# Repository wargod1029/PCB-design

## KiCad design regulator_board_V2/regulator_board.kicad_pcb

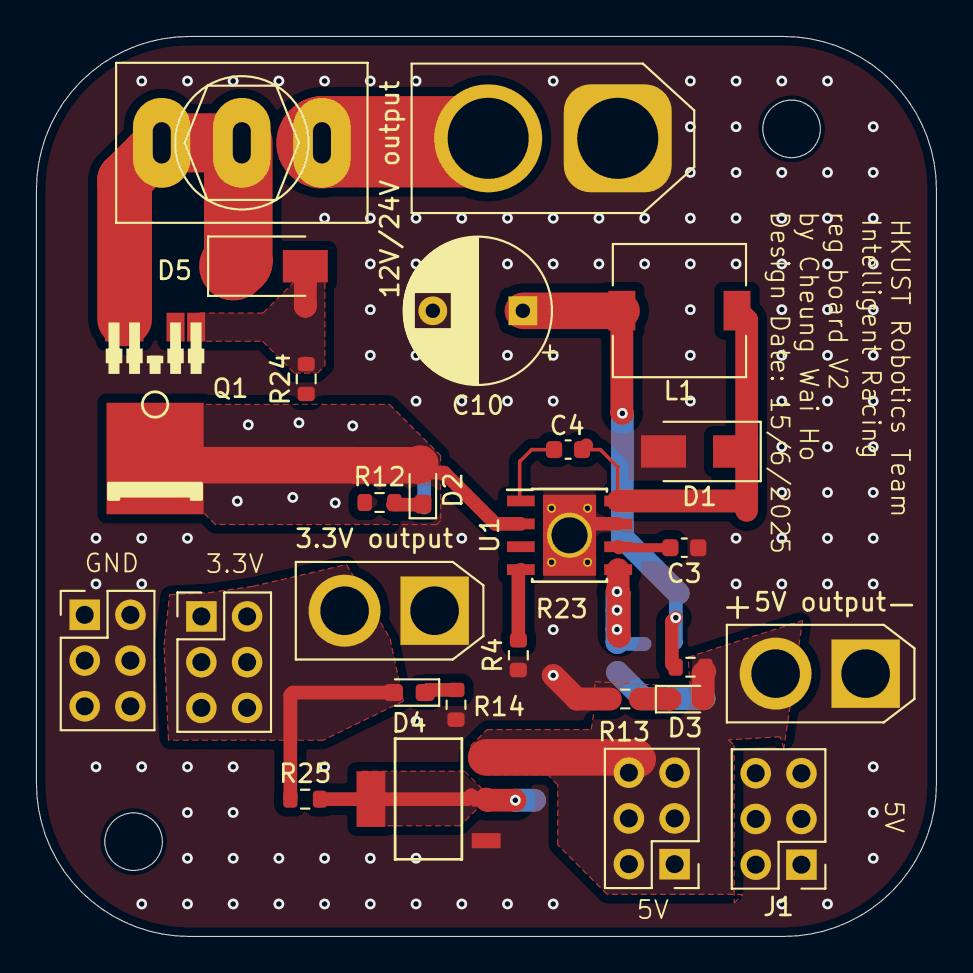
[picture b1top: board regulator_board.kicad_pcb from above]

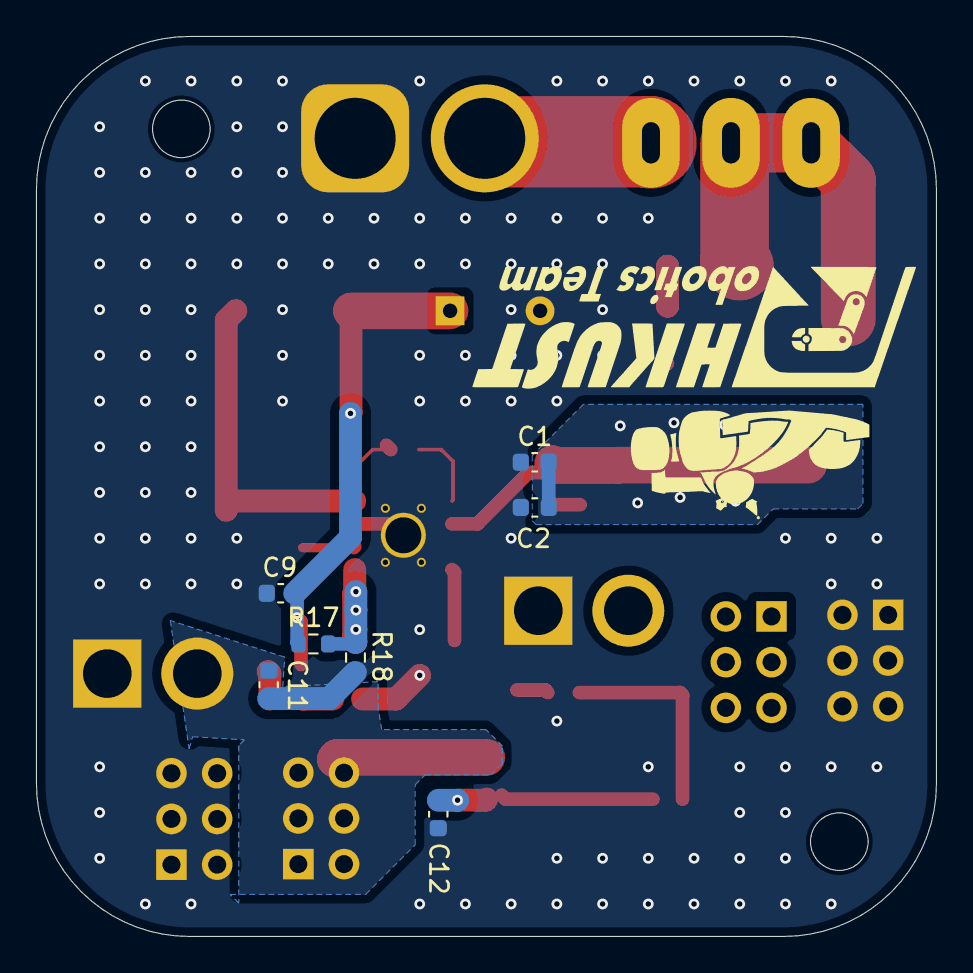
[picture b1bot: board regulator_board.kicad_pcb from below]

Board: 2 copper layers, 50.0 x 50.0 mm, 36 parts (7 on the bottom side), 17 nets.

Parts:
C1, C2: 2.2uF; C_0603_1608Metric
C3: 39pF; C_0603_1608Metric
C4: 100nF; C_0603_1608Metric
C9, C11, C12: 10uF; C_0603_1608Metric
C10: 10V 1000uF; CP_Radial_D8.0mm_P12.00mm
D1, D5: SS54; D_SMA
D2: 24V; LED_0603_1608Metric_Pad1.05x0.95mm_HandSolder
D3: 5V; LED_0603_1608Metric_Pad1.05x0.95mm_HandSolder
D4: 3.3V; LED_0603_1608Metric_Pad1.05x0.95mm_HandSolder
H2, H3: MountingHole; MountingHole_3.2mm_M3
J1, J3, J5, J6: Conn_02x03_Odd_Even_MountingPin; PinHeader_2x03_P2.54mm_Vertical
J2: 5V output; AMASS_XT30U-F_1x02_P5.0mm_Vertical
J4: 3.3V output; AMASS_XT30U-F_1x02_P5.0mm_Vertical
J7: Conn_01x02; AMASS_XT60-M_1x02_P7.20mm_Vertical
L1: 22uH; L_7.3x7.3_H3.5
Q1: SPD50P03LG; TO252-51
R4: 162k; R_0603_1608Metric
R12: 2.5k; R_0603_1608Metric
R13: 2k; R_0603_1608Metric
R14: 1.5k; R_0603_1608Metric
R17: 53.6k; R_0603_1608Metric
R18: 10.2k; R_0603_1608Metric
R23, R25: 0R; R_0603_1608Metric
R24: 10k; R_0603_1608Metric
SW1: 24V input; SW_Toggle_Blue_wSlots
U1: TPS54360DDA; TI_SO-PowerPAD-8_ThermalVias
U6: LM1117-3.3; SOT230

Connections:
+3.3V: D4.2 (A), J4.2, J5.1, J5.2, J5.3, J5.4, J5.5, J5.6, R25.1
+5V: C11.1, D3.2 (A), J2.2, J3.1, J3.2, J3.3, J3.4, J3.5, J3.6, R23.1, U6.3 (VIN)
+24V: C1.2, C2.2, D2.2 (A), Q1.5, U1.2 (VIN)
/FB: R17.1, R18.2, U1.5 (FB)
/Vin: D5.1 (K), Q1.3, Q1.4, SW1.2 (B), SW1.3 (C)
GND: C1.1, C2.1, C3.1, C9.2, C10.2, C11.2, C12.2, D1.2 (A), J1.1, J1.2, J1.3, J1.4, J1.5, J1.6, J2.1, J4.1, J6.1, J6.2, J6.3, J6.4, J6.5, J6.6, J7.1, R4.1, R12.1, R13.1, R14.1, R18.1, R24.1, U1.7 (GND), U1.9 (GNDPAD), U6.1 (ADJ/GND)
unnamed: C9.1, C10.1, L1.2, R17.2, R23.2
unnamed: C4.1, D1.1 (K), L1.1, U1.8 (SW)
unnamed: D2.1 (K), R12.2
unnamed: D3.1 (K), R13.2
unnamed: D4.1 (K), R14.2
unnamed: D5.2 (A), Q1.1, R24.2
unnamed: J7.2, SW1.1 (A)
unnamed: C4.2, U1.1 (BOOT)
unnamed: C3.2, U1.6 (COMP)
unnamed: R4.2, U1.4 (RT/CLK)
unnamed: C12.1, R25.2, U6.2 (VOUT), U6.4 (VOUT_2)

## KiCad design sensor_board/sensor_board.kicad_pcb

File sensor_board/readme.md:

# sensor_board

Brief
- 7 Infered sensors design for use in Forklift robot in Taiwan AERC competition

Key features
- Direct output analog signal from XH pin header

Repository structure
- `sensor_board.kicad_pcb` — PCB layout
- `sensor_board.kicad_sch` — Schematic
- `sensor_board.kicad_pro` — KiCad project file

Electrical overview (fill with measured values)
- Supply voltage: 3.3V to 5V

Connectors & pins
- POWER: VCC, GND
- SENSOR: direct analog voltage output (IR1 - IR7)

Fabrication notes
- PCB thickness: 1.6 mm
- Layer count: 2
- Copper thickness: 1 oz external

BOM
- Use KiCad's BOM export (`bom` plugin)

KiCad / development notes
- KiCad version used: 8.0

Designer
- Andy, Cheung

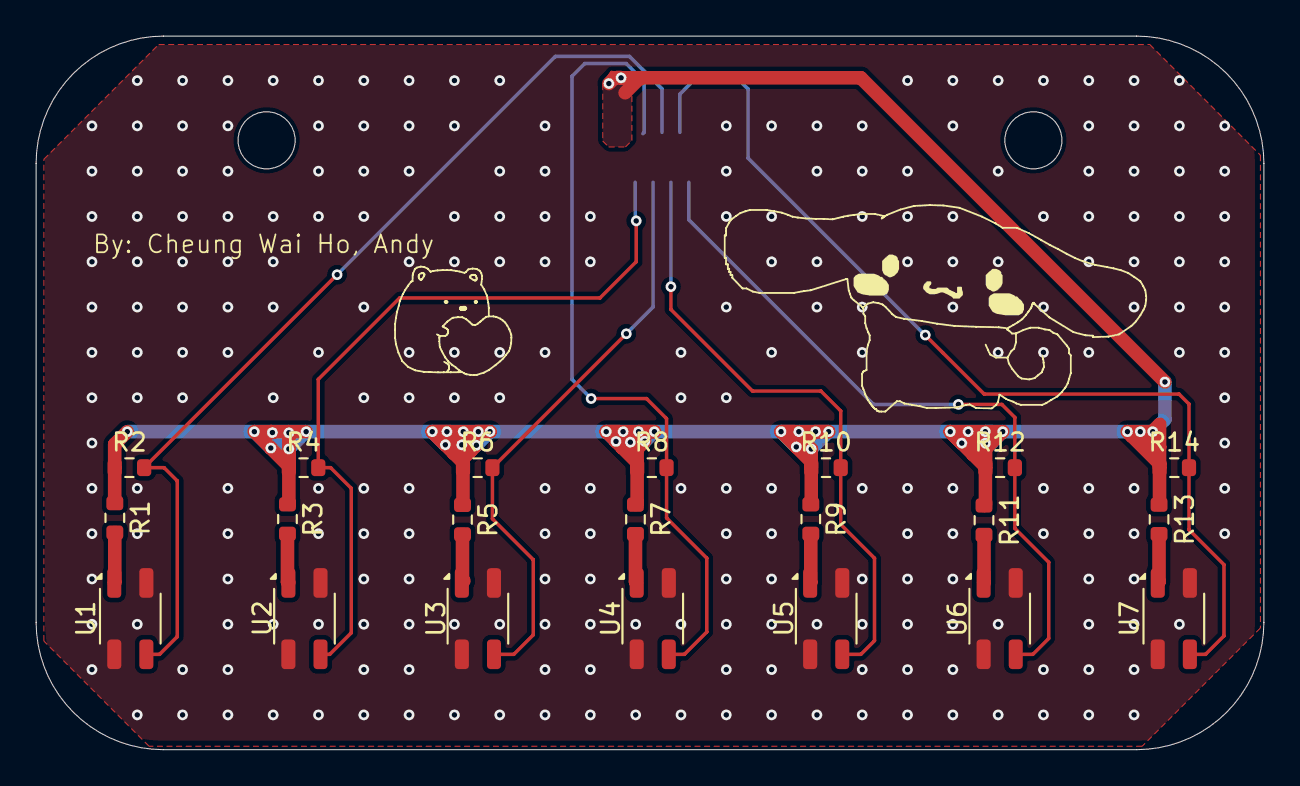
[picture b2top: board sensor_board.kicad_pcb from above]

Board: 2 copper layers, 68.8 x 40.0 mm, 24 parts (1 on the bottom side), 16 nets.

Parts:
H1, H2: MountingHole; MountingHole_3.2mm_M3
J2: FFC2A32-10-T; GCT_FFC2A32-10-T
R1, R3, R5, R7, R9, R11, R13: 100R; R_0603_1608Metric
R2, R4, R6, R8, R10, R12, R14: 53k; R_0603_1608Metric
U1, U2, U3, U4, U5, U6, U7: QRE1113GR; OnSemi_CASE100CY

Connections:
+3.3V: J2.8, J2.10, R1.1, R2.1, R3.1, R4.1, R5.1, R6.1, R7.1, R8.1, R9.1, R10.1, R11.1, R12.1, R13.1, R14.1
/IR1: J2.4, R2.2, U1.3
/IR2: J2.7, R4.2, U2.3
/IR3: J2.5, R6.2, U3.3
/IR4: J2.6, R8.2, U4.3
/IR5: J2.3, R10.2, U5.3
/IR6: J2.1, R12.2, U6.3
/IR7: J2.2, R14.2, U7.3
GND: J2.9, U1.2 (K), U1.4, U2.2 (K), U2.4, U3.2 (K), U3.4, U4.2 (K), U4.4, U5.2 (K), U5.4, U6.2 (K), U6.4, U7.2 (K), U7.4
unnamed: R1.2, U1.1 (A)
unnamed: R3.2, U2.1 (A)
unnamed: R5.2, U3.1 (A)
unnamed: R7.2, U4.1 (A)
unnamed: R9.2, U5.1 (A)
unnamed: R11.2, U6.1 (A)
unnamed: R13.2, U7.1 (A)
